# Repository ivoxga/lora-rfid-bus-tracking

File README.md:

# Bus Stop Tracking with RFID and LoRa

**A self-powered network of bus stops that tells passengers where their bus is, without mobile networks, without a server and without mains power.**

Each stop recognizes a bus that passes it by **RFID**, and passes that information to the other stops of the line by **LoRa radio**, stop to stop. Every stop has a row of LEDs, one per stop of the line, and the lit LED shows the **last stop the bus went through**. Each stop runs on **two Li-ion cells charged by a small solar panel**.

I designed both the **hardware** (a 4-layer PCB with solar charging, battery protection and power conversion) and the **firmware** (a PIC microcontroller running the RFID reader, the LoRa link, its own communication protocol with acknowledgements and retransmission, and on-site configuration). The system was built and tested as a **working proof of concept** on four stops.
 
<p align="center">
  <br>
  <em>The test setup: the stop boards (PCB with LoRa module, RFID reader and MCU), the 18650 cells, the solar panel and the RFID tags that stand in for the buses</em>
</p>

<p align="center">

</p>

---

## Contents

- [The problem](#the-problem)
- [The solution](#the-solution)
- [Repository structure](#repository-structure)
- [How it works](#how-it-works)
  - [Inside one stop](#inside-one-stop)
  - [Detecting the bus with RFID](#detecting-the-bus-with-rfid)
  - [Spreading the information along the line](#spreading-the-information-along-the-line)
  - [Frame format](#frame-format)
  - [Reliable delivery: ACK and retransmission](#reliable-delivery-ack-and-retransmission)
  - [Firmware state machine](#firmware-state-machine)
  - [Configuration on site](#configuration-on-site)
- [Hardware](#hardware)
  - [Power system](#power-system)
  - [Other subsystems](#other-subsystems)
  - [PCB design](#pcb-design)
- [Results](#results)
- [Known limitations and next steps](#known-limitations-and-next-steps)
- [Tools](#tools)
- [Author](#author)

---

## The problem

In many small towns, the bus stops have no real-time information at all. Passengers only have a printed timetable, so they wait without knowing where the bus is or whether it is late, which is especially frustrating in bad weather.

The usual solutions are expensive to run for a small network:

| | Usual approach | Drawback |
|---|---|---|
| **Detection** | GPS tracker in every bus | Active device per bus, more cost |
| **Communication** | Mobile network (GSM/4G) | Monthly subscriptions, higher consumption |
| **Processing** | Cloud server | Permanent internet, recurring costs |
| **Power** | Mains connection or disposable batteries | Civil works, or frequent battery changes |

---

## The solution

<p align="center">
  <br>
  <em>The concept: the bus is detected at a stop, and the information travels by radio from stop to stop until it reaches every stop of the line</em>
</p>

Each choice replaces one of the drawbacks above:

- **RFID for detection:** a cheap, passive tag on the bus, read exactly when the bus is at the stop. No GPS and nothing powered on the bus.
- **LoRa for communication:** a private radio link on the licence-free 868 MHz band, long range and low power, with **no subscriptions**.
- **Decentralized processing:** every stop is an **autonomous node** running the same firmware. There is no central server: each stop talks only to its two neighbours, and the information hops along the line.
- **Solar power:** two rechargeable Li-ion cells and a small solar panel, so no mains connection is needed.

**Requirements** set for the system:

| Functional | Non-functional |
|---|---|
| Identify the bus at the stop automatically | Low power consumption |
| Accept only the buses authorized for that line | Low cost |
| Record the last stop of each bus | Autonomous power (no mains) |
| Send the information to the neighbouring stops | Simple installation |
| Forward it in the right direction along the line | Robust communication between stops |
| Guarantee reliable delivery between stops | Room for future evolution |
| Show passengers the last known position | |
| Configure the system on site | |

---

## Repository structure

```
.
├── LoRa_and_RFID_with_ACK.X/       # firmware: MPLAB X project for the PIC18F27K42
│   ├── main.c                      # application: state machine, LoRa protocol, ACK, config modes
│   ├── rc522.c / rc522.h           # RC522 RFID reader driver (SPI, MIFARE commands)
│   ├── mcc_generated_files/        # peripheral drivers generated by MCC (UART, SPI, TMR0, NVM, pins)
│   └── nbproject/, Makefile        # MPLAB X project files
├── PCB/                            # hardware: Autodesk Eagle project
│   ├── Esquematico.sch             # schematic
│   ├── Esquematico.brd             # 4-layer board layout
│   ├── Librarias_EAGLE/            # component libraries used in the design
│   └── Ficheiros_JLCPCB/           # fabrication outputs: Gerbers, BOM and pick-and-place
├── images/                         # figures used in this README
└── README.md
```

---

## How it works

### Inside one stop

Every stop is the same board running the same firmware. The only difference between stops is the **stop ID** (equal to its LoRa address) and the **list of authorized buses**, both stored in the PIC's internal EEPROM.

```mermaid
flowchart LR
    TAG(["RFID tag on the bus"]) -. "13.56 MHz" .-> RFID["RC522<br/>RFID reader"]
    RFID -- "SPI" --> MCU["PIC18F27K42<br/>firmware"]
    MCU <-- "UART1 · AUX / M1" --> LORA["DX-LR03<br/>LoRa 868 MHz"]
    LORA <-. "radio" .-> NB(["Neighbouring stops<br/>MAC ± 1"])
    MCU <-- "UART2" --> USB["CH340E<br/>USB-C"]
    USB <--> PC(["PC terminal<br/>config & debug"])
    DIP["4-way DIP switch<br/>operating mode"] --> MCU
    MCU --> LED["4 LEDs<br/>one per stop"]
    MCU <--> EE[("EEPROM<br/>stop ID · bus list")]
```

| Block | Part | Role |
|---|---|---|
| Microcontroller | **PIC18F27K42** (64 MHz, 128 KB Flash, 2 UARTs) | Runs the whole firmware |
| Radio | **DX-LR03-900T30D** LoRa module | Stop-to-stop link, fixed-point addressing, configured with AT commands |
| Bus detection | **RC522** reader + **MIFARE Classic 1K** tags | Reads the bus ID when the bus is at the stop |
| PC interface | **CH340E** USB-to-UART over **USB-C** | Configuration and debug from a serial terminal |
| User interface | 4 LEDs | The lit LED shows the last stop of the bus |

### Detecting the bus with RFID

Each bus carries a **MIFARE Classic 1K** tag holding its **bus ID** (1 byte, 0–255), written in **block 4**, the first block of sector 1. Sector 0 is avoided because it holds the manufacturer data.

In the main loop, the stop keeps polling for a tag:

1. Wake the RC522 from its soft power-down.
2. **Request**: is there a tag in the field? If not, power down again and go back to idle.
3. **Anticollision → Select → Authenticate** (key A) **→ Read** block 4 **→ Halt**.
4. Power the RC522 down again, to save energy between polls.
5. Check the bus ID against the **list of authorized buses** in EEPROM. A tag that isn't on the list (another line's bus, or a stray card) is ignored.

The reader's driver was adapted to the MPLAB XC8 compiler and is organized in layers: raw SPI access, then register read/write/bit operations, then the MIFARE commands that the application calls.

### Spreading the information along the line

The stops form a **linear, bidirectional chain**. Each stop knows its own ID, and its neighbours are simply **ID − 1** (behind) and **ID + 1** (in front). The LoRa modules work in **fixed-point mode**, so each frame is addressed to one specific module, and only that module delivers it to its microcontroller.

The forwarding rules are simple, and the same on every stop:

- **The bus is read by RFID** at this stop: send the event **backwards** (DIR = back), then **forwards** (DIR = front). The first stop of the line has no neighbour behind, so it only sends forwards.
- **A frame arrives by LoRa**: forward it to the next stop **in the same direction** it was travelling (the `DIR` field).
- **Duplicates are dropped:** each stop keeps, in RAM, a table with the **last known stop of every bus**. If a frame (or a tag read) reports the stop that is already recorded, nothing is sent. This stops the information from bouncing back and forth and avoids repeated transmissions when a bus waits at a stop.
- **Invalid frames are dropped:** unknown direction, stop ID 0, or a bus that isn't authorized.

Whenever the table changes, the stop **refreshes its LEDs**, so every stop on the line ends up showing the same position.

### Frame format

- The first 3 bytes are required by the LoRa module in fixed-point mode: the **destination address** and the **channel** (24, which is 868 MHz, on every stop). The module removes them, so the receiving microcontroller only gets the **4-byte payload**.
- **ID_BUS:** the bus, as read from the tag.
- **STOP_H / STOP_L:** the ID of the stop where the bus was **detected**. It travels unchanged, so every stop learns where the bus actually is, not which neighbour told it.
- **DIR:** `0x00` to keep going front, `0x01` to keep going back.

The acknowledgement is a single byte: `0xF0` confirms a frame travelling front and `0xF1` one travelling back. They were chosen to match the `DIR` values, which makes them easy to read in the debug output.

### Reliable delivery: ACK and retransmission

Radio frames can be lost, so every data frame has to be **acknowledged by the stop that receives it**. If the acknowledgement doesn't arrive, the frame is sent again.

```mermaid
sequenceDiagram
    autonumber
    participant S2 as Stop 2
    participant S3 as Stop 3
    participant S4 as Stop 4
    Note over S2: Bus 0x01 read by RFID
    S2->>S3: DATA [01 | 0002 | front]
    Note over S3: ISR completes the frame and<br/>prepares the ACK right away
    S3-->>S2: ACK 0xF0
    Note over S3: Records bus 0x01 at stop 2,<br/>refreshes the LEDs
    S3->>S4: DATA [01 | 0002 | front]
    Note over S4: No ACK reaches stop 3
    Note over S3: 4 s timeout: retry #1
    S3->>S4: DATA [01 | 0002 | front]
    S4-->>S3: ACK 0xF0
```

How it is implemented:

- **On the receiver**, the UART interrupt collects the 4 payload bytes. As soon as the frame is complete, the interrupt **prepares the ACK** (destination MAC ± 1, depending on the direction), and the main loop **sends it before processing the frame**, so the sender gets its answer as fast as possible.
- **On the sender**, after each frame the firmware waits up to **4 seconds** for the expected ACK byte. If none arrives it **retransmits, up to 5 attempts**. If the event came from RFID, the second direction is still tried even when the first one failed.
- **No deadlock while waiting:** while a stop waits for its own ACK, it keeps **answering the ACKs owed to other stops**, so two neighbours transmitting at the same time don't block each other.
- **Partial frames are discarded:** a timer (TMR0) restarts at every received byte. If the bytes stop arriving before the frame is complete, the timer expires and the buffer is cleared, so a fragment can't corrupt the next frame.
- **Radio settings:** the LoRa module's **CRC is enabled**, so corrupted frames are rejected by the radio, and the **transmit power was tuned** for the test distances. Before sending, the firmware waits for the module's **AUX** pin to show that it is idle.

What it looks like on the debug terminal:

<table>
  <tr>
    <td align="center" width="50%"></td>
    <td align="center" width="50%"></td>
  </tr>
  <tr>
    <td align="center"><em>Stop 3: forwarding frames and exchanging ACKs in both directions</em></td>
    <td align="center"><em>No ACK: the frame is retransmitted until the ACK arrives</em></td>
  </tr>
</table>

### Firmware state machine

The application is a **state machine** in `main.c`. Received LoRa frames and pending ACKs always have priority over reading the RFID reader or entering a configuration mode.

```mermaid
stateDiagram-v2
    [*] --> IDLE
    IDLE --> ACK_SEND_PENDING: ACK owed to a neighbour
    ACK_SEND_PENDING --> LORA_COPY
    IDLE --> LORA_COPY: frame received
    IDLE --> CONFIG_LORA: DIP switch
    IDLE --> CONFIG_STOP: DIP switch
    IDLE --> RFID_CHECK: nothing pending
    RFID_CHECK --> IDLE: no tag, or bus not authorized
    RFID_CHECK --> VALIDATE: authorized bus
    LORA_COPY --> VALIDATE
    VALIDATE --> CLEANUP: invalid frame or same stop
    VALIDATE --> UPDATE: new position
    UPDATE --> TX_PREP: update table and LEDs
    TX_PREP --> TX_SEND
    TX_SEND --> WAIT_ACK
    WAIT_ACK --> TX_NEXT: expected ACK
    WAIT_ACK --> TX_RETRY: 4 s timeout
    TX_RETRY --> TX_SEND: fewer than 5 attempts
    TX_RETRY --> TX_NEXT: gave up
    TX_NEXT --> TX_PREP: other direction left
    TX_NEXT --> CLEANUP: done
    CLEANUP --> IDLE
    CONFIG_LORA --> IDLE: AT+RESET
    CONFIG_STOP --> IDLE: EXIT
```

| State | What it does |
|---|---|
| `IDLE` | Checks, in order: ACK to send, received frame, configuration switches, test mode. Otherwise goes to read the RFID |
| `ACK_SEND_PENDING` | Sends the ACK prepared by the interrupt, then processes the frame |
| `LORA_COPY` | Copies the frame out of the interrupt buffer with interrupts disabled, and extracts bus, stop and direction |
| `RFID_CHECK` | Wakes the reader, reads the tag, and filters authorized buses |
| `VALIDATE` | Drops invalid frames and positions that are already known |
| `UPDATE` | Records the bus's new stop in RAM and refreshes the LEDs |
| `TX_PREP` | Builds the frame and picks the destination: both directions for RFID, the same direction for a forwarded frame |
| `TX_SEND` / `WAIT_ACK` / `TX_RETRY` / `TX_NEXT` | Sends, waits for the ACK, retransmits, and moves on to the other direction |
| `CONFIG_LORA` / `CONFIG_STOP` | Configuration modes over USB (see below) |

### Configuration on site

A stop is configured on site with a laptop and a USB-C cable, **without reprogramming the firmware**. The **4-way DIP switch** selects the mode:

| Switch | Mode | What it does |
|---|---|---|
| 1 | **CONFIG_LORA** | Turns the board into a bridge between the PC and the LoRa module, to send AT commands (address, channel, power, CRC…). Setting the address with `AT+MAC` also saves it as the **stop ID** in EEPROM. `AT+RESET` returns to normal operation |
| 2 | **CONFIG_STOP** | Manages the list of authorized buses: `BUS+XX` adds, `BUS-XX` removes, `BUS?` lists, `EXIT` returns (IDs in hex) |
| 3 | **TEST** | Keeps sending a fixed frame to stop `0x0003`, to check the radio link quickly |
| 4 | **DEFAULT** | Writes default values from the code (stop ID and bus list) to the EEPROM at start-up, which is handy for preparing boards quickly |

What each stop keeps:

| Where | Data |
|---|---|
| EEPROM `0x00–0x01` | Stop ID (= its LoRa MAC) |
| EEPROM `0x02` | Number of authorized buses (up to 20) |
| EEPROM `0x03…` | List of authorized bus IDs |
| EEPROM `0x30` | "Initialized" marker (`0xA5`) |
| RAM | Last known stop of every bus (256 entries) |

---

## Hardware

The PCB brings all the subsystems together on one board, **134.6 × 50.5 mm, 4 layers**, made with JLCPCB's standard process. The LoRa module and the RFID reader plug into headers, and the PIC sits in a DIP-28 socket so it can be replaced easily.

### Power system

- **Solar charging:** the **BQ24650** charges the batteries from a **6 V / 2 W** panel. Its MPPSET input keeps the panel working near its **maximum power point** (set to 6 V). The charge voltage is set to **4.2 V** and the charge current to **405 mA**, within the cells' limits. Two LEDs on its STAT pins show *charging* and *charged*.
- **Batteries:** two **18650 Li-ion cells in parallel** (2 × 2400 mAh), each with its own **PTC fuse** as passive protection.
- **Active battery protection:** the **S-8261** watches voltage and current, and opens the dual MOSFET **SQ1912EH** on the negative side in case of overcharge, over-discharge, over-current or short-circuit. That is why the battery's negative (`GND_2`) and the system ground (`GND`) are separate nets, all the way to the copper planes.
- **5 V boost:** the **TPS61023** raises the battery voltage (2.5–4.2 V) to a steady **5 V**, up to 1.5 A, for the PIC, the LoRa module and the CH340E.
- **3.3 V LDO:** the **ADP150** turns 5 V into a clean **3.3 V** for the RC522 reader, which only draws about 30 mA at peak.
- **USB power:** the board can also run from the **USB-C** port. A **Schottky diode** lets VBUS feed the 5 V rail but stops the boost converter's 5 V from flowing back into the computer.

### Other subsystems

- **USB-serial interface:** a **CH340E** connects the PC to the PIC's second UART. The USB-C connector has the **5.1 kΩ pull-downs on CC1/CC2** required by the Type-C specification, so the computer recognizes the board as a device and supplies power.
- **Serial activity LEDs:** one transistor and LED per UART line (TX/RX), blinking when data flows.
- **User interface:** the **4 position LEDs** and the **DIP switch**.
- **Test points** on every important signal: `BAT+`, `GND_2`, `BQ_OUT`, `5V`, `3V3`, `GND`, `PWR_USB`, both UARTs (LoRa and PC) and the SPI bus (SDI, SDO, SCK, CS).
- **Charger jumper:** a 2-pin header between the charger output and the batteries. Removed, it lets you **measure the charge current** with an ammeter, or **isolate the charger** and run from the batteries alone.

### PCB design

<p align="center">
  <br>
  <em>The four copper layers of the board</em>
</p>

| Layer | Use |
|---|---|
| **Top** | All SMD components and most signals, with a GND pour and smaller 5 V, 3V3, `GND_2` and `BQ_OUT` areas |
| **Layer 2** | Continuous **GND plane**, with a separate island for the battery negative (`GND_2`) |
| **Layer 3** | **Power plane** split in two: `BAT+` around the charger and the boost converter, and **5 V** for the rest of the board |
| **Bottom** | Signals that didn't fit on top, plus a GND pour |

Design practices applied:

- **Manufacturing rules:** JLCPCB's 4-layer standard process parameters were loaded into Eagle's DRC before routing (through vias only, 0.35 mm minimum drill).
- **Power ICs laid out per their datasheets:** input and output capacitors right next to the pins, a **compact switching node** on both switching converters, **feedback traces** (BQ24650 `VFB`/`MPPSET`, TPS61023 `FB`) routed away from it, **wide traces** on the charge and boost paths, and **thermal vias** under the BQ24650.
- **USB differential pair** routed at controlled impedance: 0.3048 mm tracks with 0.25 mm spacing give **83.4 Ω**, inside the USB 2.0 target of 90 Ω ± 10 %. The impedance was calculated with the Saturn PCB Toolkit.
- **EMC:** continuous ground planes for short return paths, decoupling at every IC, and **rows of ground vias** along the SPI and UART lines, which act as a guard against coupling with nearby signals.

---

## Results

The system was tested on a line of **4 stops**, using the PCBs and four tags as buses.

| Test | Result |
|---|---|
| RFID write and read of the bus ID | **100 %** on 4 tags |
| LoRa addressing | Only the addressed stop receives the frame |
| Delivery along 4 stops (with ACK and retransmission) | **≈ 97 %** |
| PCB subsystems | Battery power, solar charging, USB power and USB serial all working |
| Consumption at 3.7 V | **156 mA** idle · **116 mA** between transmissions · **690 mA** peak while transmitting |
| Average consumption (15 buses per stop per day, worst case of 5 attempts per direction) | **≈ 157 mA**, because the system spends over 99 % of the time idle |
| Autonomy without sun (2 × 2400 mAh) | **≈ 30.6 hours** |
| Solar charge current | **255 mA** with a lab supply at 6 V, **220 mA** outdoors with a clear sky, both above the average consumption |

In short, the decentralized RFID + LoRa architecture works as a proof of concept: the bus is detected, only authorized buses are accepted, the last stop is recorded correctly at every stop, and a stop runs for more than a day without sun while the panel covers the consumption during the day.

---

## Known limitations and next steps

These are the open points of the current version, in order of priority:

1. **Battery over-current protection is disabled in this board revision.** The S-8261 trips when the voltage across the protection MOSFETs exceeds 100 mV. With the SQ1912EH's on-resistance (about 0.45 Ω for the pair), that happens at about **220 mA**, below the **350 mA** inrush of the TPS61023 at start-up, so the protection cut the power on every boot. As a workaround, the S-8261's VM pin is tied to VSS, which disables the over-current detection only. **Fix:** MOSFETs with an on-resistance below about **22 mΩ** each, so the full 2.25 A boost input current stays under the 100 mV threshold.
2. **The TX/RX activity LEDs are inverted.** NPN transistors were fitted where PNP ones were needed. The UART lines idle high, so the LEDs stay on and blink *off*. The fix is swapping the transistor type in the next revision.
3. **RFID range.** The RC522 with HF proximity tags was the right low-cost choice to prove the concept, but it reads one tag at a time at a few centimetres. A real installation needs **UHF RFID**, which reads at several metres and can see more than one bus at once.
4. **Field testing.** Long outdoor tests are still needed: temperature, humidity, interference, solar charging in poor light, and later formal EMC tests and an IP-rated enclosure.
5. **Lower power.** The LoRa module's sleep mode isn't used yet. A module that **integrates the LoRa radio and the microcontroller** would cut consumption considerably.
6. **Security.** LoRa frames are not encrypted, which is fine for a proof of concept but required for production.

---

## Tools

- **Firmware:** MPLAB X IDE, MPLAB XC8 compiler, MPLAB Code Configurator (MCC), PICkit 5
- **Hardware:** Autodesk Eagle (schematic and 4-layer layout), Saturn PCB Toolkit (impedance), JLCPCB (fabrication)
- **Testing:** CoolTerm serial terminal, multimeter and bench power supply

---

## Author

**Ivo Azevedo**: hardware design (schematic and PCB) and firmware.

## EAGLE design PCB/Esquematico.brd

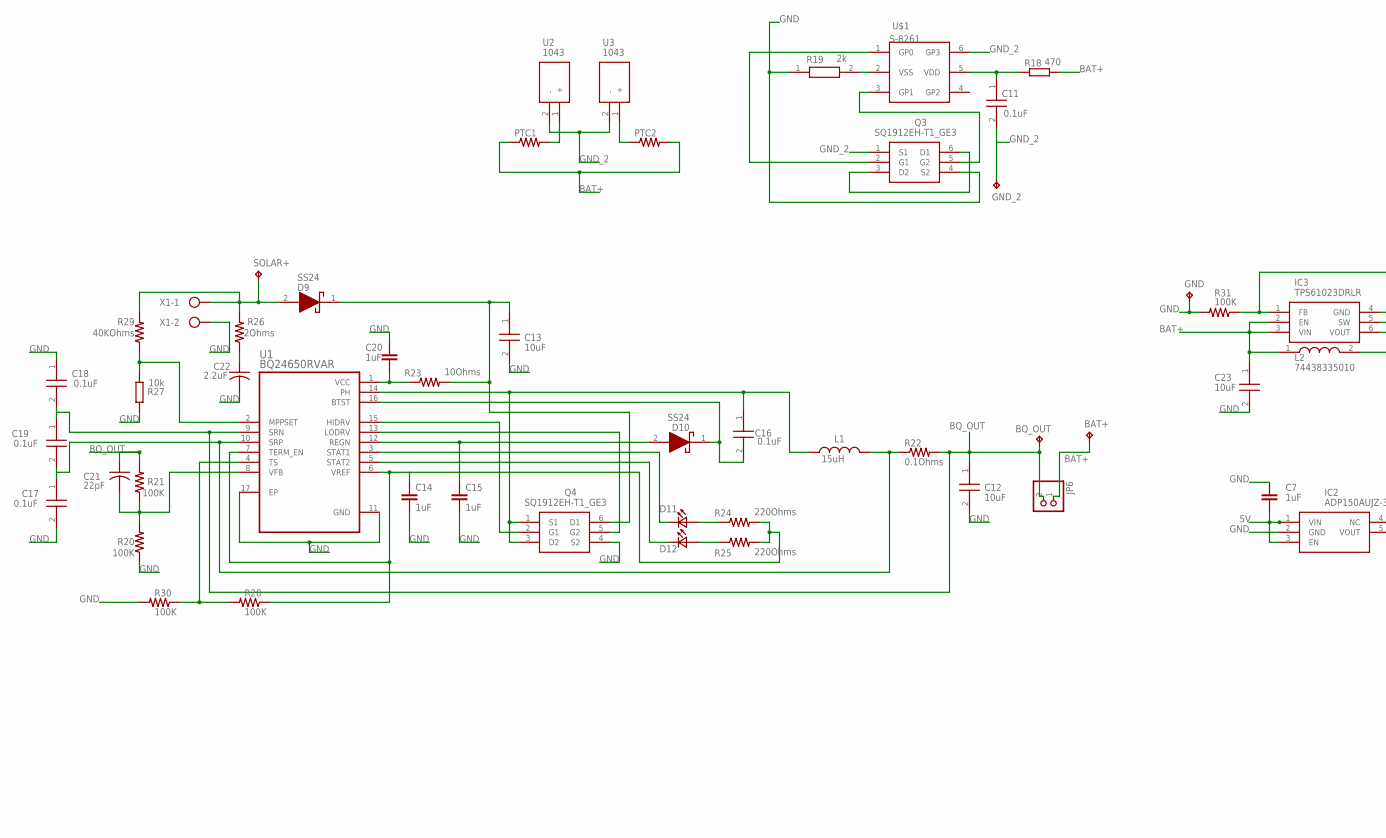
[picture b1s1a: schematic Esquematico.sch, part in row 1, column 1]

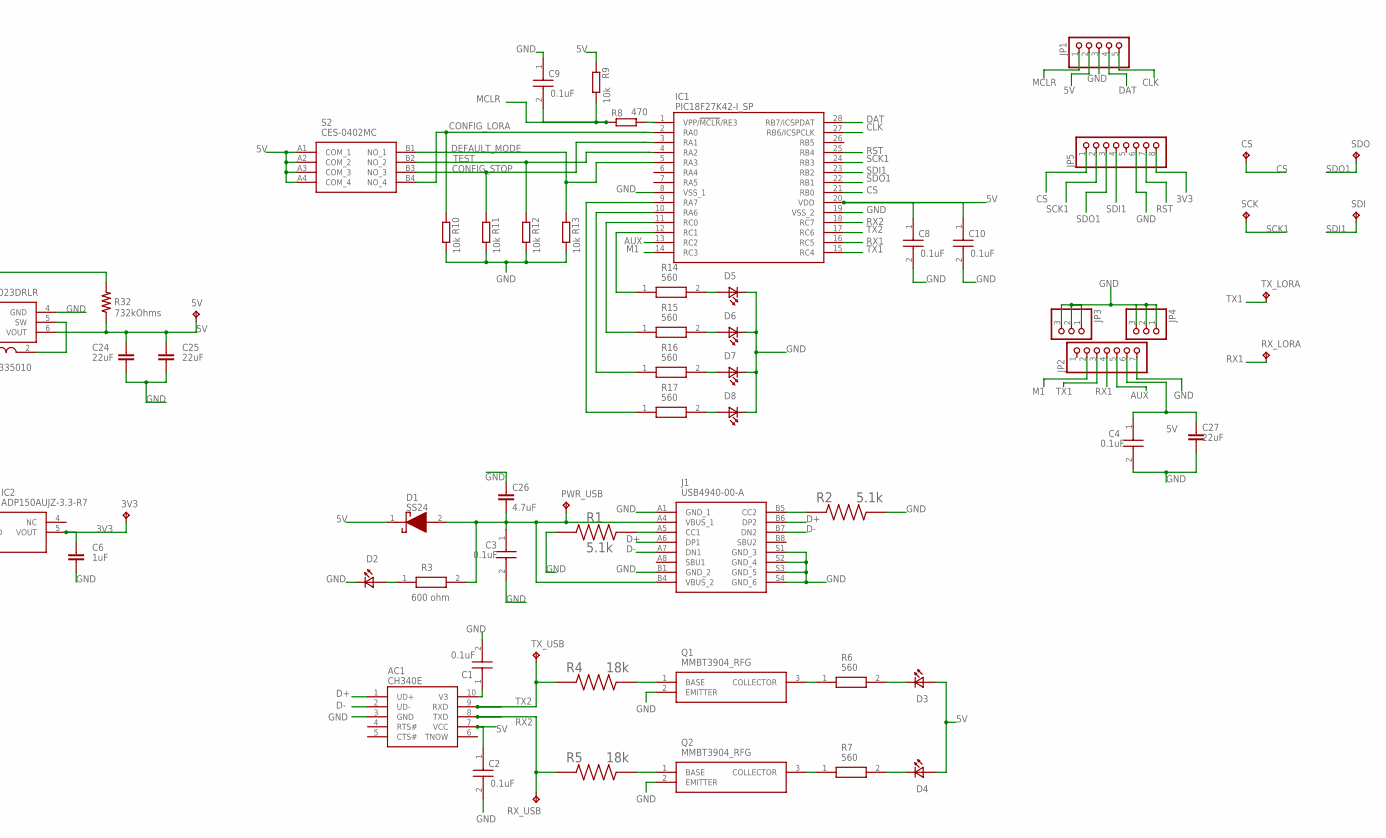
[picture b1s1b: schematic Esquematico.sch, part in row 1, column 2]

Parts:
3V3, 5V: TPB1,27; B1,27
AC1: CH340E; SOP50P490X100-10N
BAT+: TPB1,27; B1,27
BQ_OUT: TPB1,27; B1,27
C1, C2, C3, C4, C8, C9, C10, C11, C16, C17, C18, C19: 0.1uF; CAPC0402X22N
C6, C7, C14, C15, C20: 1uF; C0805K
C12, C13, C23: 10uF; CAPC2013X113N
C21: 22pF; C0603
C22: 2.2uF; C0603
C24, C25, C27: 22uF; C1210K
C26: 4.7uF; C0402
CS: TPB1,27; B1,27
D1, D9, D10: SS24; DIOM5436X247N
D2, D3, D4, D5, D6, D7, D8, D11, D12: LTST-C193KGKT-5A; 0603
GND: TPB1,27; B1,27
GND_2: TPB1,27; B1,27
IC1: PIC18F27K42-I_SP; DIP794W56P254L3486H508Q28N
IC2: ADP150AUJZ-3.3-R7; SOT95P280X100-5N
IC3: TPS61023DRLR; SOTFL50P160X60-6N
J1: USB4940-00-A; USB494000A
JP1: PINHD-1X5; 1X05
JP2: PINHD-1X7; 1X07
JP3, JP4: PINHD-1X3; 1X03
JP5: PINHD-1X8; 1X08
JP6: PINHD-1X2; 1X02
L1: 15uH; WE-PD2A_7850
L2: 74438335010; INDPM3030X150N
PTC1, PTC2: R-US_R0603; R0603
PWR_USB: TPB1,27; B1,27
Q1, Q2: MMBT3904_RFG; SOT95P237X112-3N
Q3, Q4: SQ1912EH-T1_GE3; SQ1912EHT1_GE3
R1, R2: 5.1k; RESC1608X55N
R3: 600 ohm; RESC2012X60N
R4, R5: 18k; RESC1608X55N
R6, R7, R14, R15, R16, R17: 560; RESC1608X50N
R8, R18: 470; R1206
R9, R10, R11, R12, R13, R27: 10k; R1206
R19: 2k; RESC1608X50N
R20, R21, R28, R30, R31: 100K; R0402
R22: 0.1Ohms; R0805
R23: 10Ohms; R1206W
R24, R25: 220Ohms; R0402
R26: 2Ohms; R2512W
R29: 40KOhms; R0805
R32: 732kOhms; R0402
RX_LORA: TPB1,27; B1,27
RX_USB: TPB1,27; B1,27
S2: CES-0402MC; CES0402MC
SCK: TPB1,27; B1,27
SDI: TPB1,27; B1,27
SDO: TPB1,27; B1,27
SOLAR+: TPB1,27; B1,27
TX_LORA: TPB1,27; B1,27
TX_USB: TPB1,27; B1,27
U1: BQ24650RVAR; QFN50P350X350X100-17N
U2, U3: 1043
U$1: S-8261; SOT23-6
X1: V+; W237-102

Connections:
3V3: 3V3.TP, C6.1, IC2.5 (VOUT), JP5.8
5V: 5V.TP, AC1.7 (VCC), C2.1, C4.1, C7.2, C8.1, C10.1, C24.1, C25.1, C27.1, D1.1 (K), D3.2 (A2), D4.2 (A2), IC1.20 (VDD), IC2.1 (VIN), IC2.3 (EN), IC3.6 (VOUT), JP1.2, JP2.6, R9.1, R32.1, S2.A1 (COM_1), S2.A2 (COM_2), S2.A3 (COM_3), S2.A4 (COM_4)
AUX: IC1.13 (RC2), JP2.5
BAT+: BAT+.TP, C23.1, IC3.2 (EN), IC3.3 (VIN), JP6.1, L2.1, PTC1.1, PTC2.2, R18.2
BQ_OUT: BQ_OUT.TP, C12.1, C18.2, C19.1, C21.1, JP6.2, R21.2, R22.2, U1.9 (SRN)
CLK: IC1.27 (RB6/ICSPCLK), JP1.5
CONFIG_LORA: IC1.2 (RA0), R10.1, S2.B4 (NO_4)
CONFIG_STOP: IC1.3 (RA1), R11.1, S2.B3 (NO_3)
CS: CS.TP, IC1.21 (RB0), JP5.1
D+: AC1.1 (UD+), J1.A6 (DP1), J1.B6 (DP2)
D-: AC1.2 (UD-), J1.A7 (DN1), J1.B7 (DN2)
DAT: IC1.28 (RB7/ICSPDAT), JP1.4
DEFAULT_MODE: IC1.5 (RA3), R13.1, S2.B1 (NO_1)
GND: AC1.3 (GND), C1.2, C2.2, C3.2, C4.2, C6.2, C7.1, C8.2, C9.1, C10.2, C12.2, C13.2, C14.2, C15.2, C17.2, C18.1, C20.1, C22.2, C23.2, C24.2, C25.2, C26.1, C27.2, D2.1 (K2), D5.1 (K2), D6.1 (K2), D7.1 (K2), D8.1 (K2), GND.TP, IC1.8 (VSS_1), IC1.19 (VSS_2), IC2.2 (GND), IC3.4 (GND), J1.A1 (GND_1), J1.B1 (GND_2), J1.S1 (GND_3), J1.S2 (GND_4), J1.S3 (GND_5), J1.S4 (GND_6), JP1.3, JP2.7, JP3.1, JP3.2, JP3.3, JP4.1, JP4.2, JP4.3, JP5.6, Q1.2 (EMITTER), Q2.2 (EMITTER), Q3.4 (S2), Q4.4 (S2), R1.1, R2.2, R10.2, R11.2, R12.2, R13.2, R19.1, R20.1, R27.1, R30.2, R31.2, U1.11 (GND), U1.17 (EP), X1.2
GND_2: C11.2, GND_2.TP, Q3.1 (S1), U2.2 (-), U3.2 (-), U$1.6 (GP3)
M1: IC1.14 (RC3), JP2.2
MCLR: C9.2, JP1.1, R8.1, R9.2
unnamed: J1.A5 (CC1), R1.2
unnamed: Q1.1 (BASE), R4.2
unnamed: C3.1, C26.2, D1.2 (A), J1.A4 (VBUS_1), J1.B4 (VBUS_2), PWR_USB.TP, R3.2
unnamed: J1.B5 (CC2), R2.1
unnamed: D2.2 (A2), R3.1
unnamed: AC1.10 (V3), C1.1
unnamed: Q2.1 (BASE), R5.2
unnamed: IC1.9 (RA7), R17.1
unnamed: IC1.10 (RA6), R16.1
unnamed: Q1.3 (COLLECTOR), R6.1
unnamed: IC1.11 (RC0), R15.1
unnamed: IC1.12 (RC1), R14.1
unnamed: Q2.3 (COLLECTOR), R7.1
unnamed: D3.1 (K2), R6.2
unnamed: D4.1 (K2), R7.2
unnamed: IC1.1 (VPP/!MCLR!/RE3), R8.2
unnamed: Q3.2 (G1), U$1.1 (GP0)
unnamed: D5.2 (A2), R14.2
unnamed: D6.2 (A2), R15.2
unnamed: D7.2 (A2), R16.2
unnamed: D8.2 (A2), R17.2
unnamed: C11.1, R18.1, U$1.5 (VDD)
unnamed: Q3.5 (G2), U$1.3 (GP1)
unnamed: Q3.3 (D2), Q3.6 (D1)
unnamed: C20.2, R23.1, U1.1 (VCC)
unnamed: R19.2, U$1.2 (VSS)
unnamed: C16.1, L1.1, Q4.1 (S1), Q4.3 (D2), U1.14 (PH)
unnamed: C17.1, C19.2, L1.2, R22.1, U1.10 (SRP)
unnamed: C14.1, R24.2, R25.2, R28.1, U1.6 (VREF), U1.7 (TERM_EN)
unnamed: R27.2, R29.1, U1.2 (MPPSET)
unnamed: R28.2, R30.1, U1.4 (TS)
unnamed: C16.2, D10.1 (K), U1.16 (BTST)
unnamed: C21.2, R20.2, R21.1, U1.8 (VFB)
unnamed: C13.1, D9.1 (K), Q4.6 (D1), R23.2
unnamed: D9.2 (A), R26.2, R29.2, SOLAR+.TP, X1.1
unnamed: C22.1, R26.1
unnamed: D11.2 (A2), R24.1
unnamed: D12.2 (A2), R25.1
unnamed: D11.1 (K2), U1.3 (STAT1)
unnamed: D12.1 (K2), U1.5 (STAT2)
unnamed: C15.1, D10.2 (A), U1.12 (REGN)
unnamed: Q4.2 (G1), U1.15 (HIDRV)
unnamed: Q4.5 (G2), U1.13 (LODRV)
unnamed: PTC1.2, U2.1 (+)
unnamed: PTC2.1, U3.1 (+)
unnamed: IC3.5 (SW), L2.2
unnamed: IC3.1 (FB), R31.1, R32.2
RST: IC1.25 (RB4), JP5.7
RX1: IC1.16 (RC5), JP2.4, RX_LORA.TP
RX2: AC1.8 (TXD), IC1.18 (RC7), R5.1, RX_USB.TP
SCK1: IC1.24 (RB3), JP5.2, SCK.TP
SDI1: IC1.23 (RB2), JP5.4, SDI.TP
SDO1: IC1.22 (RB1), JP5.3, SDO.TP
TEST: IC1.4 (RA2), R12.1, S2.B2 (NO_2)
TX1: IC1.15 (RC4), JP2.3, TX_LORA.TP
TX2: AC1.9 (RXD), IC1.17 (RC6), R4.1, TX_USB.TP

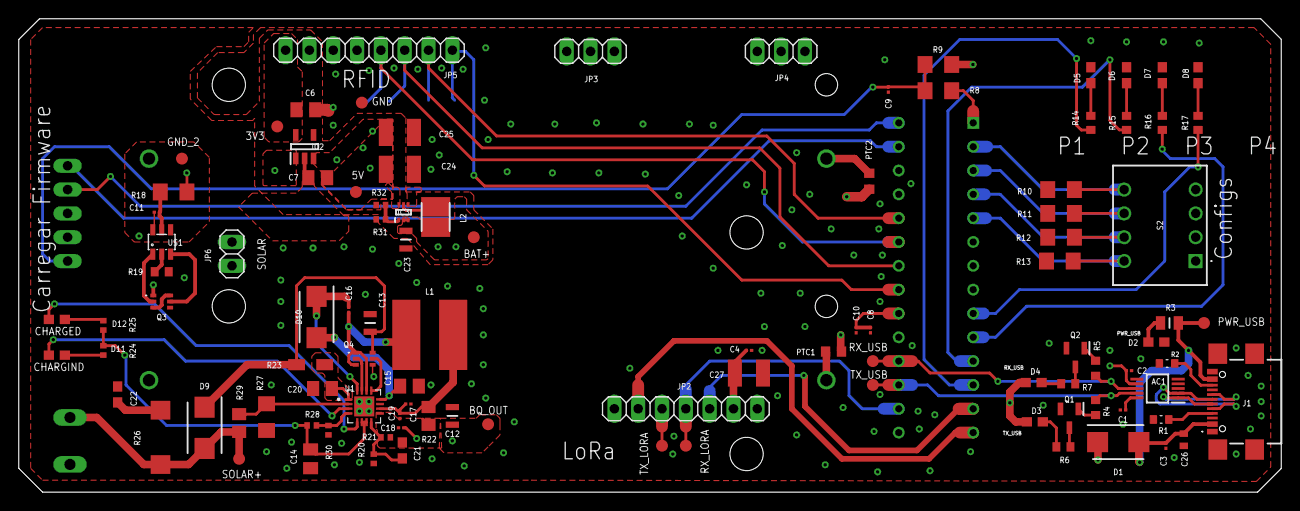
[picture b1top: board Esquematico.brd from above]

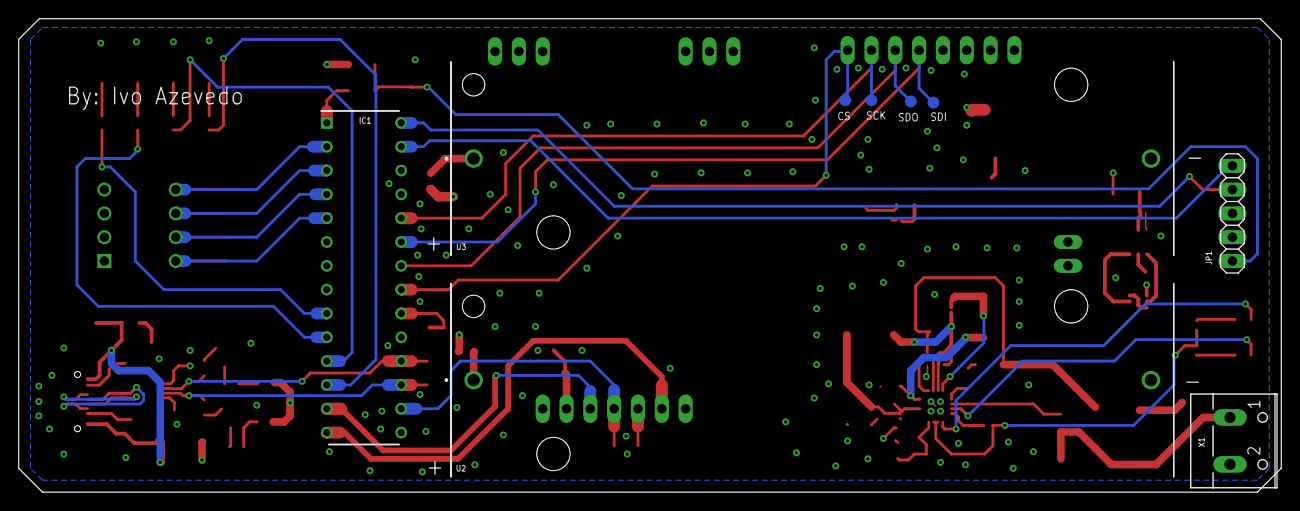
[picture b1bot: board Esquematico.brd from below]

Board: 4 copper layers, 134.6 x 50.5 mm, 111 parts (9 on the bottom side), 73 nets.

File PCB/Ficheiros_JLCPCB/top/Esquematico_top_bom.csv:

Comment,Designator,Footprint,LCSC Part #
,PTC1 PTC2,R0603,
0.1Ohms,R22,R0805,
0.1uF,C1 C2 C3 C4 C8 C9 C10 C11 C16 C17 C18 C19,CAPC0402X22N,
1uF,C6 C7 C14 C15 C20,C0805K,
2.2uF,C22,C0603,
2Ohms,R26,R2512W,
2k,R19,RESC1608X50N,
4.7uF,C26,C0402,
5.1k,R1 R2,RESC1608X55N,
10Ohms,R23,R1206W,
10k,R9 R10 R11 R12 R13 R27,R1206,
10uF,C12 C13 C23,CAPC2013X113N,
15uH,L1,WE-PD2A_7850,
18k,R4 R5,RESC1608X55N,
22pF,C21,C0603,
22uF,C24 C25 C27,C1210K,
40KOhms,R29,R0805,
100K,R20 R21 R28 R30 R31,R0402,
220Ohms,R24 R25,R0402,
470,R8 R18,R1206,
560,R6 R7 R14 R15 R16 R17,RESC1608X50N,
600 ohm,R3,RESC2012X60N,
732kOhms,R32,R0402,
74438335010,L2,INDPM3030X150N,
ADP150AUJZ-3.3-R7,IC2,SOT95P280X100-5N,
BQ24650RVAR,U1,QFN50P350X350X100-17N,
CH340E,AC1,SOP50P490X100-10N,
LTST-C193KGKT-5A,D2 D3 D4 D5 D6 D7 D8 D11 D12,0603,
MMBT3904_RFG,Q1 Q2,SOT95P237X112-3N,
S-8261,U$1,SOT23-6,
SQ1912EH-T1_GE3,Q3 Q4,SQ1912EHT1_GE3,
SS24,D1 D9 D10,DIOM5436X247N,
TPB1 27,3V3,B1 27,
TPB1 27,5V,B1 27,
TPB1 27,BAT+,B1 27,
TPB1 27,BQ_OUT,B1 27,
TPB1 27,GND,B1 27,
TPB1 27,GND_2,B1 27,
TPB1 27,PWR_USB,B1 27,
TPB1 27,RX_LORA,B1 27,
TPB1 27,RX_USB,B1 27,
TPB1 27,SOLAR+,B1 27,
TPB1 27,TX_LORA,B1 27,
TPB1 27,TX_USB,B1 27,
TPS61023DRLR,IC3,SOTFL50P160X60-6N,
USB4940-00-A,J1,USB494000A,

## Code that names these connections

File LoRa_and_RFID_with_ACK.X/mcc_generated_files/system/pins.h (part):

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// get/set RA0 aliases
#define lora_config_TRIS                 TRISAbits.TRISA0
#define lora_config_LAT                  LATAbits.LATA0
#define lora_config_PORT                 PORTAbits.RA0
#define lora_config_WPU                  WPUAbits.WPUA0
#define lora_config_OD                   ODCONAbits.ODCA0
#define lora_config_ANS                  ANSELAbits.ANSELA0
#define lora_config_SetHigh()            do { LATAbits.LATA0 = 1; } while(0)
#define lora_config_SetLow()             do { LATAbits.LATA0 = 0; } while(0)
#define lora_config_Toggle()             do { LATAbits.LATA0 = ~LATAbits.LATA0; } while(0)
#define lora_config_GetValue()           PORTAbits.RA0
#define lora_config_SetDigitalInput()    do { TRISAbits.TRISA0 = 1; } while(0)
#define lora_config_SetDigitalOutput()   do { TRISAbits.TRISA0 = 0; } while(0)
#define lora_config_SetPullup()          do { WPUAbits.WPUA0 = 1; } while(0)
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// get/set RA1 aliases
#define stop_config_TRIS                 TRISAbits.TRISA1
#define stop_config_LAT                  LATAbits.LATA1
#define stop_config_PORT                 PORTAbits.RA1
#define stop_config_WPU                  WPUAbits.WPUA1
#define stop_config_OD                   ODCONAbits.ODCA1
#define stop_config_ANS                  ANSELAbits.ANSELA1
#define stop_config_SetHigh()            do { LATAbits.LATA1 = 1; } while(0)
#define stop_config_SetLow()             do { LATAbits.LATA1 = 0; } while(0)
#define stop_config_Toggle()             do { LATAbits.LATA1 = ~LATAbits.LATA1; } while(0)
#define stop_config_GetValue()           PORTAbits.RA1
#define stop_config_SetDigitalInput()    do { TRISAbits.TRISA1 = 1; } while(0)
#define stop_config_SetDigitalOutput()   do { TRISAbits.TRISA1 = 0; } while(0)
#define stop_config_SetPullup()          do { WPUAbits.WPUA1 = 1; } while(0)
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// get/set RA2 aliases
#define test_lora_mode_TRIS                 TRISAbits.TRISA2
#define test_lora_mode_LAT                  LATAbits.LATA2
#define test_lora_mode_PORT                 PORTAbits.RA2
#define test_lora_mode_WPU                  WPUAbits.WPUA2
#define test_lora_mode_OD                   ODCONAbits.ODCA2
#define test_lora_mode_ANS                  ANSELAbits.ANSELA2
#define test_lora_mode_SetHigh()            do { LATAbits.LATA2 = 1; } while(0)
#define test_lora_mode_SetLow()             do { LATAbits.LATA2 = 0; } while(0)
#define test_lora_mode_Toggle()             do { LATAbits.LATA2 = ~LATAbits.LATA2; } while(0)
#define test_lora_mode_GetValue()           PORTAbits.RA2
#define test_lora_mode_SetDigitalInput()    do { TRISAbits.TRISA2 = 1; } while(0)
#define test_lora_mode_SetDigitalOutput()   do { TRISAbits.TRISA2 = 0; } while(0)
#define test_lora_mode_SetPullup()          do { WPUAbits.WPUA2 = 1; } while(0)
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// get/set RA3 aliases
#define dev_TRIS                 TRISAbits.TRISA3
#define dev_LAT                  LATAbits.LATA3
#define dev_PORT                 PORTAbits.RA3
#define dev_WPU                  WPUAbits.WPUA3
#define dev_OD                   ODCONAbits.ODCA3
#define dev_ANS                  ANSELAbits.ANSELA3
#define dev_SetHigh()            do { LATAbits.LATA3 = 1; } while(0)
#define dev_SetLow()             do { LATAbits.LATA3 = 0; } while(0)
#define dev_Toggle()             do { LATAbits.LATA3 = ~LATAbits.LATA3; } while(0)
#define dev_GetValue()           PORTAbits.RA3
#define dev_SetDigitalInput()    do { TRISAbits.TRISA3 = 1; } while(0)
#define dev_SetDigitalOutput()   do { TRISAbits.TRISA3 = 0; } while(0)
#define dev_SetPullup()          do { WPUAbits.WPUA3 = 1; } while(0)
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// get/set RA6 aliases
#define led3_TRIS                 TRISAbits.TRISA6
#define led3_LAT                  LATAbits.LATA6
#define led3_PORT                 PORTAbits.RA6
#define led3_WPU                  WPUAbits.WPUA6
#define led3_OD                   ODCONAbits.ODCA6
#define led3_ANS                  ANSELAbits.ANSELA6
#define led3_SetHigh()            do { LATAbits.LATA6 = 1; } while(0)
#define led3_SetLow()             do { LATAbits.LATA6 = 0; } while(0)
#define led3_Toggle()             do { LATAbits.LATA6 = ~LATAbits.LATA6; } while(0)
#define led3_GetValue()           PORTAbits.RA6
#define led3_SetDigitalInput()    do { TRISAbits.TRISA6 = 1; } while(0)
#define led3_SetDigitalOutput()   do { TRISAbits.TRISA6 = 0; } while(0)
#define led3_SetPullup()          do { WPUAbits.WPUA6 = 1; } while(0)
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// get/set RA7 aliases
#define led4_TRIS                 TRISAbits.TRISA7
#define led4_LAT                  LATAbits.LATA7
#define led4_PORT                 PORTAbits.RA7
#define led4_WPU                  WPUAbits.WPUA7
#define led4_OD                   ODCONAbits.ODCA7
#define led4_ANS                  ANSELAbits.ANSELA7
#define led4_SetHigh()            do { LATAbits.LATA7 = 1; } while(0)
#define led4_SetLow()             do { LATAbits.LATA7 = 0; } while(0)
#define led4_Toggle()             do { LATAbits.LATA7 = ~LATAbits.LATA7; } while(0)
#define led4_GetValue()           PORTAbits.RA7
#define led4_SetDigitalInput()    do { TRISAbits.TRISA7 = 1; } while(0)
#define led4_SetDigitalOutput()   do { TRISAbits.TRISA7 = 0; } while(0)
#define led4_SetPullup()          do { WPUAbits.WPUA7 = 1; } while(0)
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// get/set RB0 aliases
#define cs_TRIS                 TRISBbits.TRISB0
#define cs_LAT                  LATBbits.LATB0
#define cs_PORT                 PORTBbits.RB0
#define cs_WPU                  WPUBbits.WPUB0
#define cs_OD                   ODCONBbits.ODCB0
#define cs_ANS                  ANSELBbits.ANSELB0
#define cs_SetHigh()            do { LATBbits.LATB0 = 1; } while(0)
#define cs_SetLow()             do { LATBbits.LATB0 = 0; } while(0)
#define cs_Toggle()             do { LATBbits.LATB0 = ~LATBbits.LATB0; } while(0)
#define cs_GetValue()           PORTBbits.RB0
#define cs_SetDigitalInput()    do { TRISBbits.TRISB0 = 1; } while(0)
#define cs_SetDigitalOutput()   do { TRISBbits.TRISB0 = 0; } while(0)
#define cs_SetPullup()          do { WPUBbits.WPUB0 = 1; } while(0)
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// get/set RB1 aliases
#define mosi_TRIS                 TRISBbits.TRISB1
#define mosi_LAT                  LATBbits.LATB1
#define mosi_PORT                 PORTBbits.RB1
#define mosi_WPU                  WPUBbits.WPUB1
#define mosi_OD                   ODCONBbits.ODCB1
#define mosi_ANS                  ANSELBbits.ANSELB1
#define mosi_SetHigh()            do { LATBbits.LATB1 = 1; } while(0)
#define mosi_SetLow()             do { LATBbits.LATB1 = 0; } while(0)
#define mosi_Toggle()             do { LATBbits.LATB1 = ~LATBbits.LATB1; } while(0)
#define mosi_GetValue()           PORTBbits.RB1
#define mosi_SetDigitalInput()    do { TRISBbits.TRISB1 = 1; } while(0)
#define mosi_SetDigitalOutput()   do { TRISBbits.TRISB1 = 0; } while(0)
#define mosi_SetPullup()          do { WPUBbits.WPUB1 = 1; } while(0)
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// get/set RB2 aliases
#define miso_TRIS                 TRISBbits.TRISB2
#define miso_LAT                  LATBbits.LATB2
#define miso_PORT                 PORTBbits.RB2
#define miso_WPU                  WPUBbits.WPUB2
#define miso_OD                   ODCONBbits.ODCB2
#define miso_ANS                  ANSELBbits.ANSELB2
#define miso_SetHigh()            do { LATBbits.LATB2 = 1; } while(0)
#define miso_SetLow()             do { LATBbits.LATB2 = 0; } while(0)
#define miso_Toggle()             do { LATBbits.LATB2 = ~LATBbits.LATB2; } while(0)
#define miso_GetValue()           PORTBbits.RB2
#define miso_SetDigitalInput()    do { TRISBbits.TRISB2 = 1; } while(0)
#define miso_SetDigitalOutput()   do { TRISBbits.TRISB2 = 0; } while(0)
#define miso_SetPullup()          do { WPUBbits.WPUB2 = 1; } while(0)
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// get/set RB3 aliases
#define sck_TRIS                 TRISBbits.TRISB3
#define sck_LAT                  LATBbits.LATB3
#define sck_PORT                 PORTBbits.RB3
#define sck_WPU                  WPUBbits.WPUB3
#define sck_OD                   ODCONBbits.ODCB3
#define sck_ANS                  ANSELBbits.ANSELB3
#define sck_SetHigh()            do { LATBbits.LATB3 = 1; } while(0)
#define sck_SetLow()             do { LATBbits.LATB3 = 0; } while(0)
#define sck_Toggle()             do { LATBbits.LATB3 = ~LATBbits.LATB3; } while(0)
#define sck_GetValue()           PORTBbits.RB3
#define sck_SetDigitalInput()    do { TRISBbits.TRISB3 = 1; } while(0)
#define sck_SetDigitalOutput()   do { TRISBbits.TRISB3 = 0; } while(0)
#define sck_SetPullup()          do { WPUBbits.WPUB3 = 1; } while(0)
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// get/set RB4 aliases
#define rst_TRIS                 TRISBbits.TRISB4
#define rst_LAT                  LATBbits.LATB4
#define rst_PORT                 PORTBbits.RB4
#define rst_WPU                  WPUBbits.WPUB4
#define rst_OD                   ODCONBbits.ODCB4
#define rst_ANS                  ANSELBbits.ANSELB4
#define rst_SetHigh()            do { LATBbits.LATB4 = 1; } while(0)
#define rst_SetLow()             do { LATBbits.LATB4 = 0; } while(0)
#define rst_Toggle()             do { LATBbits.LATB4 = ~LATBbits.LATB4; } while(0)
#define rst_GetValue()           PORTBbits.RB4
#define rst_SetDigitalInput()    do { TRISBbits.TRISB4 = 1; } while(0)
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

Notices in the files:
LoRa_and_RFID_with_ACK.X/mcc_generated_files/system/pins.h:
© [2026] Microchip Technology Inc. and its subsidiaries.
parts and their libraries:
Eagle_WE-PD2A: Copyright: Würth Elektronik
